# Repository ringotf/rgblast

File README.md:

# RGBlast - RGB + Audio To HDMI For Sega Master System & Genesis/Mega Drive

- Master System : (See "sms" branch) - Work in progress! 
- Genesis/Mega Drive : (See "md" branch)  - Work in progress! 

## Description

The original RGBlast project was a 2-bit flash analog-to-digital converter RP2040-based video capture for the Sega Mega-Drive/Genesis... which is ideal for capturing the RGB222 video signals from the Sega Master System!

This prototype has been updated so that instead of using 9 comparators (3 per RGB channel), the channels are multiplexed and switched mid-pixel for sampling so only 3 comparators are used with 3 SPDT analog switches.

## Features

- RGB222 Video Capture
- Mono Audio Capture
- HDMI output using [ikjordan PicoDVI fork](https://github.com/ikjordan/picodvi)

## To-Do

- Update schematics
- Fix wobbly vertical lines
- 50/60hz switch?
- Design PCB
- ???

## Demo Video

----
----

Original Readme:

# SEGA Genesis RGBlast Processor - RP2040 code & Schematics

A hardware design for capturing RGB direct from a SEGA Genesis and delivering it via USB to a PC.

## Description

The SEGA Genesis RGBlast Processor is a Raspi Pico based video capture device that directly digitizes the RGB output of a SEGA Genesis and delivers it via USB to a host computer.

The analog channels (RGB) are captured via a 2 bit Flash ADC which is half hardware and half PIO program.

To build a functioning version from scratch, please see the circuit-schematics folder. PCB Schematics will be released if/when a proven design is achieved. Here is one of the latest prototypes as built from the schematic:

At the moment this device is capable of 6 bits per pixel, ~30FPS. Video is fairly noisy in the test PCBs which have been constructed:

https://user-images.githubusercontent.com/127321359/224463316-a748747a-c26d-4245-b84a-755739763bbe.mp4

## Getting Started

Building this to a Raspi Pico requires the C/C++ SDK: https://www.raspberrypi.com/documentation/microcontrollers/c_sdk.html

It is possible to test this device with more commonly available parts. For example utilizing LM393s as comparators (rather than the MCP6569) on a breadboard will work, but the image will be very noisy/sloppy.

You could also utilize the Raspi Pico's built-in USB (instead of the FTDI external device.) Framerates will be significantly lower.

Please see the Rust client project for the software which can receive and decode the incoming 6bpp stream to a simple application window.

## Authors

Contributors names and contact info

JP Stringham
[@jotapeh](https://mastodon.gamedev.place/@jotapeh)

## Version History

* 0.1
    * Initial Release

## License

This project is licensed under the MIT License - see the LICENSE file for details

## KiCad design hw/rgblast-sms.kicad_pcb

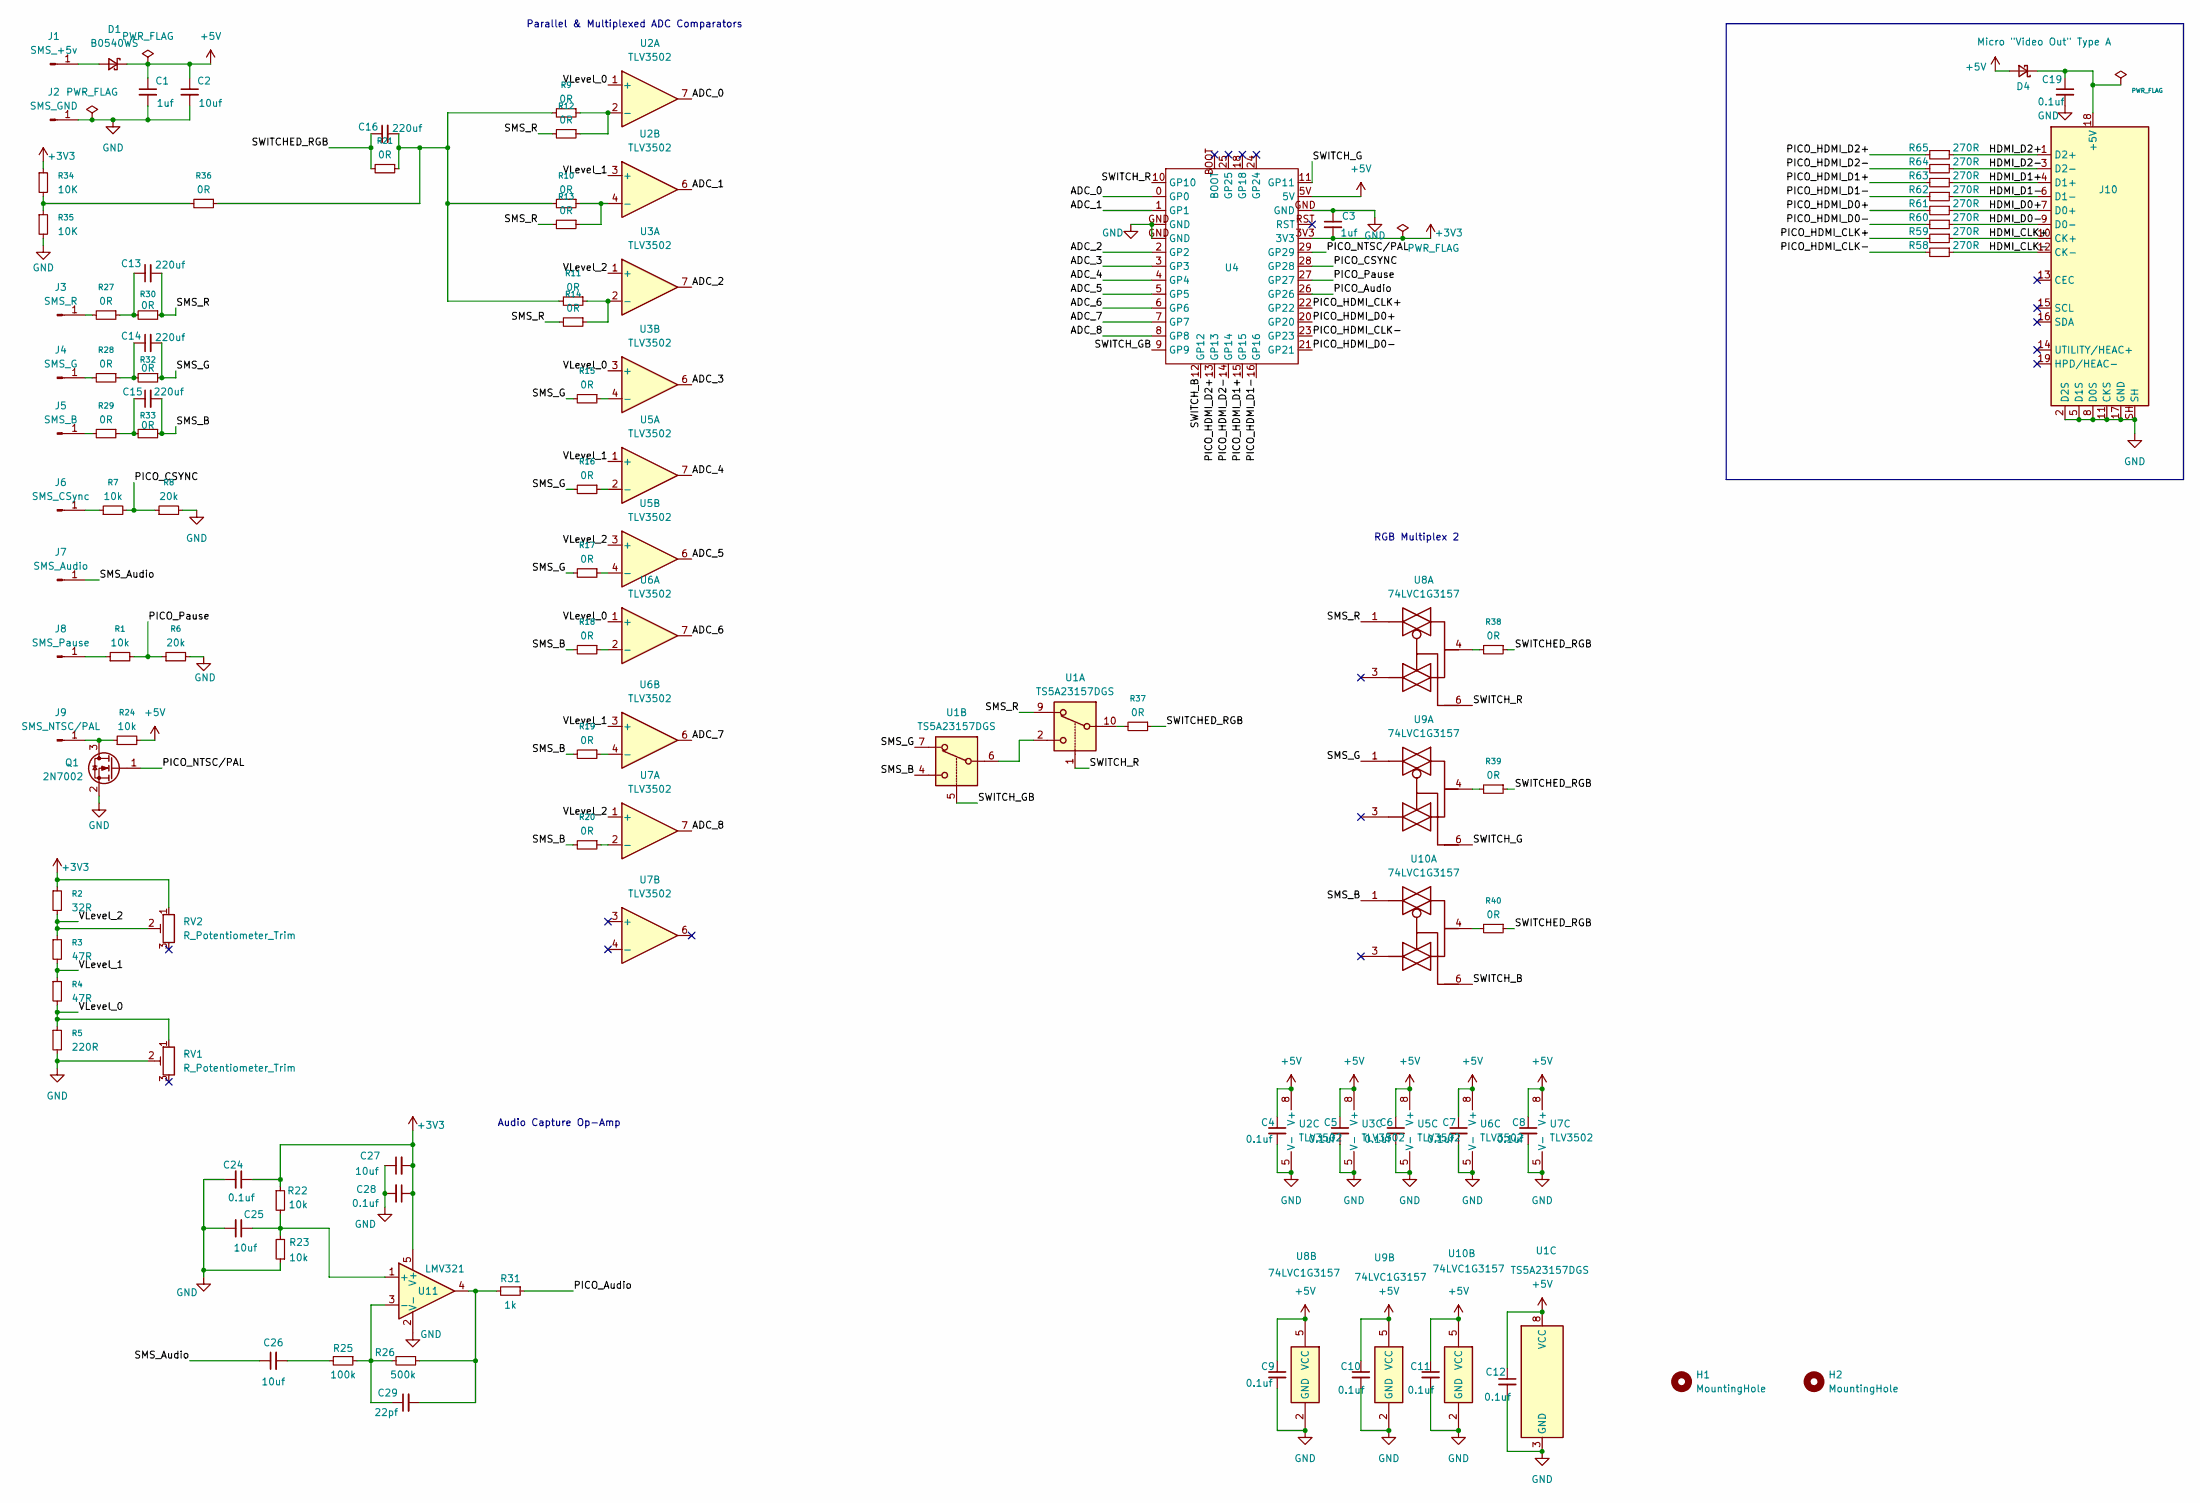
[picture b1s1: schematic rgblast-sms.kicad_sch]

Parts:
C1, C3: 1uf; C_0402_1005Metric_Pad0.74x0.62mm_HandSolder
C2, C27: 10uf; C_0402_1005Metric_Pad0.74x0.62mm_HandSolder
C4, C5, C6, C7, C8, C9, C10, C11, C12, C19, C28: 0.1uf; C_0402_1005Metric_Pad0.74x0.62mm_HandSolder
C13, C14, C15, C16: 220uf; C_0805_2012Metric_Pad1.18x1.45mm_HandSolder
C24: 0.1uf; C_0805_2012Metric_Pad1.18x1.45mm_HandSolder
C25, C26: 10uf; C_0805_2012Metric_Pad1.18x1.45mm_HandSolder
C29: 22pf; C_0805_2012Metric_Pad1.18x1.45mm_HandSolder
D1, D4: B0540WS; D_SOD-323_HandSoldering
H1, H2: MountingHole; ToolingHole_1.152mm
J1: SMS_+5v; TestPoint_Pad_D1.0mm
J2: SMS_GND; TestPoint_Pad_D1.0mm
J3: SMS_R; TestPoint_Pad_D1.0mm
J4: SMS_G; TestPoint_Pad_D1.0mm
J5: SMS_B; TestPoint_Pad_D1.0mm
J6: SMS_CSync; TestPoint_Pad_D1.0mm
J7: SMS_Audio; TestPoint_Pad_D1.0mm
J8: SMS_Pause; TestPoint_Pad_D1.0mm
J9: SMS_NTSC/PAL; TestPoint_Pad_D1.0mm
J10: Micro "Video Out" Type A; HDMI_A_Molex_208658-1001_Horizontal
Q1: 2N7002; SOT-23
R1, R7, R22, R23, R24: 10k; R_0805_2012Metric_Pad1.20x1.40mm_HandSolder
R2: 32R; R_0805_2012Metric_Pad1.20x1.40mm_HandSolder
R3, R4: 47R; R_0805_2012Metric_Pad1.20x1.40mm_HandSolder
R5: 220R; R_0805_2012Metric_Pad1.20x1.40mm_HandSolder
R6, R8: 20k; R_0805_2012Metric_Pad1.20x1.40mm_HandSolder
R9, R10, R11, R12, R13, R14, R15, R16, R17, R18, R19, R20, R21, R27, R28, R29, R30, R32, R33, R36, R37, R38, R39, R40: 0R; R_0805_2012Metric_Pad1.20x1.40mm_HandSolder
R25: 100k; R_0805_2012Metric_Pad1.20x1.40mm_HandSolder
R26: 500k; R_0805_2012Metric_Pad1.20x1.40mm_HandSolder
R31: 1k; R_0805_2012Metric_Pad1.20x1.40mm_HandSolder
R34, R35: 10K; R_0805_2012Metric_Pad1.20x1.40mm_HandSolder
R58, R59, R60, R61, R62, R63, R64, R65: 270R; R_0402_1005Metric_Pad0.72x0.64mm_HandSolder
RV1, RV2: R_Potentiometer_Trim; Potentiometer_Bourns_3296W_Vertical
U1: TS5A23157DGS; TSSOP-10_3x3mm_P0.5mm
U2, U3, U5, U6, U7: TLV3502; SOIC-8_3.9x4.9mm_P1.27mm
U4: pro_micro_rp2040
U8, U9, U10: 74LVC1G3157; SOT-23-6_Handsoldering
U11: LMV321; SOT-23-5_HandSoldering

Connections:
+3V3: C3.2, C24.1, C27.2, C28.1, R2.1, R22.1, R34.1, RV2.1, U4.3V3, U11.5 (V+)
+5V: C1.1, C2.1, C4.1, C5.1, C6.1, C7.1, C8.1, C9.1, C10.1, C11.1, C12.1, D1.1 (K), D4.2 (A), R24.2, U1.8 (VCC), U2.8 (V+), U3.8 (V+), U4.5V, U5.8 (V+), U6.8 (V+), U7.8 (V+), U8.5 (VCC), U9.5 (VCC), U10.5 (VCC)
/ADC_0: U2.7, U4.0 (GP0)
/ADC_1: U2.6, U4.1 (GP1)
/ADC_2: U3.7, U4.2 (GP2)
/ADC_3: U3.6, U4.3 (GP3)
/ADC_4: U4.4 (GP4), U5.7
/ADC_5: U4.5 (GP5), U5.6
/ADC_6: U4.6 (GP6), U6.7
/ADC_7: U4.7 (GP7), U6.6
/ADC_8: U4.8 (GP8), U7.7
/HDMI_CLK+: J10.10 (CK+), R59.1
/HDMI_CLK-: J10.12 (CK-), R58.1
/HDMI_D0+: J10.7 (D0+), R61.1
/HDMI_D0-: J10.9 (D0-), R60.1
/HDMI_D1+: J10.4 (D1+), R63.1
/HDMI_D1-: J10.6 (D1-), R62.1
/HDMI_D2+: J10.1 (D2+), R65.1
/HDMI_D2-: J10.3 (D2-), R64.1
/PICO_Audio: R31.1, U4.26 (GP26)
/PICO_CSYNC: R7.2, R8.1, U4.28 (GP28)
/PICO_HDMI_CLK+: R59.2, U4.22 (GP22)
/PICO_HDMI_CLK-: R58.2, U4.23 (GP23)
/PICO_HDMI_D0+: R61.2, U4.20 (GP20)
/PICO_HDMI_D0-: R60.2, U4.21 (GP21)
/PICO_HDMI_D1+: R63.2, U4.15 (GP15)
/PICO_HDMI_D1-: R62.2, U4.16 (GP16)
/PICO_HDMI_D2+: R65.2, U4.13 (GP13)
/PICO_HDMI_D2-: R64.2, U4.14 (GP14)
/PICO_NTSC/PAL: Q1.1 (G), U4.29 (GP29)
/PICO_Pause: R1.2, R6.1, U4.27 (GP27)
/SMS_Audio: C26.1, J7.1 (Pin_1_1)
/SMS_B: C15.2, R18.2, R19.2, R20.2, R33.1, U1.4, U10.1
/SMS_G: C14.2, R15.2, R16.2, R17.2, R32.1, U1.7, U9.1
/SMS_R: C13.2, R12.2, R13.2, R14.2, R30.1, U1.9, U8.1
/SWITCHED_RGB: C16.1, R21.2, R37.1, R38.1, R39.1, R40.1
/SWITCH_B: U4.12 (GP12), U10.6
/SWITCH_G: U4.11 (GP11), U9.6
/SWITCH_GB: U1.5, U4.9 (GP9)
/SWITCH_R: U1.1, U4.10 (GP10), U8.6
/VLevel_0: R4.2, R5.1, RV1.1, U2.1 (+), U3.3 (+), U6.1 (+)
/VLevel_1: R3.2, R4.1, U2.3 (+), U5.1 (+), U6.3 (+)
/VLevel_2: R2.2, R3.1, RV2.2, U3.1 (+), U5.3 (+), U7.1 (+)
GND: C1.2, C2.2, C3.1, C4.2, C5.2, C6.2, C7.2, C8.2, C9.2, C10.2, C11.2, C12.2, C19.2, C24.2, C25.2, C27.1, C28.2, J2.1 (Pin_1_1), J10.2 (D2S), J10.5 (D1S), J10.8 (D0S), J10.11 (CKS), J10.17 (GND), J10.SH, Q1.2 (S), R5.2, R6.2, R8.2, R23.1, R35.2, RV1.2, U1.3 (GND), U2.5 (V-), U3.5 (V-), U4.GND, U5.5 (V-), U6.5 (V-), U7.5 (V-), U8.2 (GND), U9.2 (GND), U10.2 (GND), U11.2 (V-)
unnamed: C13.1, R27.1, R30.2
unnamed: C14.1, R28.1, R32.2
unnamed: C15.1, R29.1, R33.2
unnamed: C16.2, R9.2, R10.2, R11.2, R21.1, R36.1
unnamed: C26.2, R25.2
unnamed: C29.2, R26.1, R31.2, U11.4
unnamed: D1.2 (A), J1.1 (Pin_1_1)
unnamed: C19.1, D4.1 (K), J10.18 (+5V)
unnamed: J3.1 (Pin_1_1), R27.2
unnamed: J4.1 (Pin_1_1), R28.2
unnamed: J5.1 (Pin_1_1), R29.2
unnamed: J6.1 (Pin_1_1), R7.1
unnamed: J8.1 (Pin_1_1), R1.1
unnamed: J9.1 (Pin_1_1), Q1.3 (D), R24.1
unnamed: R34.2, R35.1, R36.2
unnamed: R37.2, U1.10
unnamed: R38.2, U8.4
unnamed: R39.2, U9.4
unnamed: R40.2, U10.4
unnamed: U1.2, U1.6
unnamed: R9.1, R12.1, U2.2 (-)
unnamed: R10.1, R13.1, U2.4 (-)
unnamed: R11.1, R14.1, U3.2 (-)
unnamed: R15.1, U3.4 (-)
unnamed: R16.1, U5.2 (-)
unnamed: R17.1, U5.4 (-)
unnamed: R18.1, U6.2 (-)
unnamed: R19.1, U6.4 (-)
unnamed: R20.1, U7.2 (-)
unnamed: C25.1, R22.2, R23.2, U11.1 (+)
unnamed: C29.1, R25.1, R26.2, U11.3 (-)

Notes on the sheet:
RGB Multiplex 2
Parallel & Multiplexed ADC Comparators
Audio Capture Op-Amp

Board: 2 copper layers, 97 parts (0 on the bottom side), 75 nets, no tracks yet.

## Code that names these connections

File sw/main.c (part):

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
const uint SWITCH_DRAIN_PIN = 4;

const uint SWITCH_R_PIN = 9;
const uint SWITCH_GB_PIN = 10;
const uint SWITCH_G_PIN = 10;
const uint SWITCH_B_PIN = 11;



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/*
bool __not_in_flash_func(adc_callback_test)(struct repeating_timer *t)
{
    adc_select_input(sms_audio_pin);
    uint16_t adc_value = adc_read();
    printf("adc_value: %d\n", adc_value);
    
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	}

	adc_init();
	adc_gpio_init(sms_audio_pin); //enable adc and disabled gpio on these pins
    //adc_gpio_init(27);
    //adc_gpio_init(28);
    //adc_gpio_init(29);
	
	adc_set_temp_sensor_enabled(false);

    //adc_select_input(sms_audio_pin);

	//add_repeating_timer_ms(1, adc_callback_test, NULL, &dvi_audio_timer);

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
    //sm_config_set_sideset_pins(&c, RED_NOT_ENABLE_PIN);
    
    pio_gpio_init(pio, SWITCH_R_PIN);
    pio_gpio_init(pio, SWITCH_G_PIN);
    pio_gpio_init(pio, SWITCH_B_PIN);
    //pio_gpio_init(pio, SWITCH_GB_PIN);


    pio_sm_set_consecutive_pindirs(pio, sm, SWITCH_R_PIN, 3, true);
    sm_config_set_sideset_pins(&c, SWITCH_R_PIN);
    
    //pio_gpio_init(pio, SWITCH_DRAIN_PIN);
    //pio_sm_set_consecutive_pindirs(pio, sm, SWITCH_DRAIN_PIN, 1, true);
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
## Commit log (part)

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2026-05-02 Updated .gitignore
2026-05-02 Added libdvi for "dvi" video output with audio.
    Added audio capture.
    Added DMA with lookup table to write directly to framebuffer from PIO reading all 9 flash ADC inputs.
    Renamed project and source files.
2026-05-05 Moved code to sw directory
2026-05-05 Corrected pixel capture timing to fix wobbly vertical lines.
    Added PAL60 video config to use PAL timing with NTSC resolution.
2026-05-07 50/60hz switching works with 4 quick presses of pause button and config saved after each change.
    restarting pio/dma after the change to reconfigure doesnt work - breaks audio, probably breaking interrupts, as does enabling stdio_init_all()
2026-05-19 Added some docs and started updating kicad project.
2026-06-07 Tweaked pixel read timing for use with TS5A23157 analog switches for multiplexed rgb.
    Tried fixing issues with core 0 crashing after startup - still weird things happening though.
2026-06-08 Timings and sideset pins for SN74LVC1G3157 analog switches for multiplexed rgb
2026-06-22 Changes for md rgb capture, including separate build config.
    Added 15bit RGB555 capture pio.
    Added 15bpp output for libdvi.
2026-06-23 Updated readme.
